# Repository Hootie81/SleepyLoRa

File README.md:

# SleepyLora Blinds System

A low-power wireless smart blinds system using LoRa to enable low power yet fast response to commands - 100% local control.

In July 2023 I set out the key requirements for the project
- 100% local control - no 3rd party servers etc.
- solar powered with up to 3days bad weather.
- back driveable without breaking.
- secure
- be cheap

This system is 100% local, no external access required at all.

A 2.5w 380mm x 70mm thin film flexible panel is enough to keep a 2000mah battery fully charged with less than 2 hours a day of sun. the 2000mah battery lasts about 10 days with no panel connected.

Key design requirement was for the blinds to still operate by hand, so a mechanism was developed that disengages the motor from the actuator once the move command is complete. [See disengage mechanism video](https://youtu.be/guv8YasCPMQ?si=FenjIrAAZN0NFrJr)

Position is sensed using a linear potentiometer thats connected to the actualing arm, so the blinds always know their position.

The actuators now use a PID controller to target a specified time for each move, this allows the motor to run significantly quieter and allows syncronsation of blinds with different operating forces/friction. All PID, PWM and timing settings are customisable.

All data packets are AES128 encrypted and hardened against replay attacks using 1 second interval TOTP, so no-one can open your blinds but you.
Costs are kept low by using cheap modules form china, assembled onto custom PCB's and housed in 3d printed parts.
The wired slaves are powered by the master, thus only a single battery and solar panel per system and a significant reduction in actuator cost too. 

This project includes electronics designs, firmware, and 3D printable parts for a complete DIY solution.

- [3D Parts Assembly Video](https://youtu.be/qfTnw-1N8DM?si=_8NIrLeuZx0titTB)
- [Electronics Assembly Video](https://youtu.be/dtDF-GL67Ew?si=iw6Ndi3xGu8mUtQ1)

This has been a couple of years in the making, and still very much a work in progress. If you find this project useful, please consider supporting my work:

Your support helps me keep building and maintaining open-source projects like this. Thank you!

---

### System

- **Gateway**:  
  Heltec Wireless Stick Lite V3, Connects to WiFi and MQTT, relays commands between Home Assistant and LoRa network. 
  Exposes a web portal for configuration and security key generation

- **Master**:  
  Blind actuator with a Heltec Wireless Stick Lite V3, voltage booster, motor driver, position sensor and RS485 module.
  Powered from a single cell lipo battery or USB.
  Can supply power to and control multiple slave devices via RS485.
  Exposes a web portal for configuration and firmware updates. (via button press or mqtt command)

- **Slave**:  
  Blind actuator with an ESP32-c3 module, motor driver, position sensor and RS485 module. 
  Powered by the Master
  Exposes a web portal for address configuration and OTA updates. (via button press or mqtt command)
  Connects to the master using a flat 6core telephone cable terminated with 4pin JST XH2.54 connectors
  
---

## Features

- **Long-range LoRa wireless communication**
- **Easy WiFi and MQTT Setup**
- **Easy key generation and sharing**
- **Home Assistant auto-discovery**
- **OTA firmware updates**
- **Configurable RS485 slave addressing**
- **Easy Open/Closed position setting via web portal**
- **PWM speed control with PID controller for quiet operation**
- **Auto calibration feature for disengage mechanism**
- **Low-power operation** 
- **3D-printable hardware** 
- **Easy to assemble electronics**
- **Open-source** 

---

## Project Structure

- **3d_prints/**  
  STL files for all mechanical parts 

- **Electronics/**  
  KiCad schematics, PCB layouts, and Gerber files for the master and slave boards.

- **SleepyLoraGateway/**  
  Firmware for the LoRa gateway device. Handles MQTT, Home Assistant integration, and LoRa communication. 

- **SleepyLoraMaster/**  
  Firmware for the master device, an actuator for one set of shutters, with the capability to power and control several slave devices via RS485.

- **SleepyLoraSlave/**  
  Firmware for the slave device, an actuator for one set of shutters and reports position/status.

---

## Getting Started

- Order all the parts/modules from Aliexpress, list in `Electronics/`
- Order PCB/s using the KiCad files in `Electronics/`
- Print and assemble the required parts from `3d_prints/`
- Solder the modules onto the PCB's
- Install electronics in 3d printed base
- Flash the appropriate firmware to each device:
  - Gateway: `SleepyLoraGateway/`
  - Master: `SleepyLoraMaster/`
  - Slave: `SleepyLoraSlave/`
- Configure the Gateway
  - Connect to the SleepyLoraGateway AP (pw: blind1234)
  - Set the WiFi, MQTT and NTP server information.
  - Set LoRa Region
  - Generate keys and download them. 
  - Save and reboot.
  - Gateway Connects to WiFi, MQTT and Sync's its time.
  - Gateway Publishes gateway metric discovery info and publishes data.
- Configure the Master/s
  - Connect to the SleeplyLoRaMaster AP (pw: blind1234)
  - Load the keys file downloaded above
  - Set Open and Closed limits
  - Save and reboot
  - Master sync's time with gateway
  - Master transmits Device metrics and status to Gateway.
  - Gateway publishes Blind discovery info, subscribes to MQTT topics, and publishes data every 60sec.
  - Master will transmit device metrics and status every minute.
- Check your HA MQTT integration, the Gatway, device and blind will magically appear after a minute or so. 
- Optionally - configure the slave/save
  - Connect the slave to the master 
  - Press the reset button on the master
  - Master will scan for slaves on initial bootup
  - Master transmits slave status to Gateway.
  - Gateway publishes Blind discovery info, subscribes to MQTT topics, and publishes data every 60sec.
  - Open web portal via MQTT or from the master web portal
  - Set Open and Closed limits
  - Master will poll slave and transmit status every minute.
  - Optionally - if a second slave is required
    - press the "Open Web Portal" button on the slave device in HomeAssistant
	- Connect to the SleeplyLoRaSlave AP (pw: blind1234)
	- Change the slave number
	- Save to flash
    - Scan for slaves via the master's web portal (Or press the reset button on the master)
    - Master will rescan for slaves

---

## Documentation

- Each firmware folder contains its own README with build and usage instructions.
- For wiring, assembly, and setup, see my videos on youtube or open an issue for help.

---

## ToDo

- Update slave firmware to use new motor controller library and updated web portal.
- Add feature to get/set all blind settings via MQTT.
- Design an enclosure to the battery and charger modules.
- Make an injection moulding option for the plastic parts.

---

## License

This project is open-source under the MIT License.  
See [LICENSE](LICENSE) for details.

---

## Credits

- Hardware, firmware, and 3D design by Chris Huitema
- Built with [PlatformIO](https://platformio.org/), [KiCad](https://kicad.org/), and [ESPAsyncWebServer](https://github.com/me-no-dev/ESPAsyncWebServer)

---

**Happy hacking and smart shading!**

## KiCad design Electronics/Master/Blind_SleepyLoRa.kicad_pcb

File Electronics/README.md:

# Electronics Folder — SleepyLoRa Project

This folder contains all the electronics design files, schematics, PCB layouts, and bills of materials (BOM) for the SleepyLoRa Blinds System. The electronics are designed to be easy to assemble, cost-effective, and reliable for DIY smart blinds control.

## Structure
- **bom.csv** — Common components and extras used across all devices (master, slave, gateway, etc.).
- **Master/** — Schematics, PCB layout, and device-specific BOM for the SleepyLoRaMaster (blind actuator/master controller).
- **Slave/** — Schematics, PCB layout, and device-specific BOM for the SleepyLoRaSlave (slave blind actuator).

Each device folder contains:
- KiCad project files (`.pro`, `.sch`, `.kicad_pcb`, etc.)
- Gerber files for PCB manufacturing
- Device-specific BOM (bill of materials)

## How to Use
1. Review `bom.csv` for the list of common components and extras needed for all devices.
2. For each device (Master, Slave, Gateway):
   - Open the corresponding folder for full schematics, PCB layout, and device-specific BOM.
   - Use the KiCad files to view or modify the design.
   - Use the Gerber files to order PCBs from your preferred manufacturer.
   - Use the device-specific BOM to order parts for that device.
3. Assemble the PCBs according to the schematics and BOMs.

## Notes
- All designs are open-source and provided as-is for DIY use.
- If you make improvements or modifications, please consider contributing back to the project!

## License
SPDX-License-Identifier: MIT

---
For questions or support, open an issue on the main [SleepyLoRa GitHub repository](https://github.com/Hootie81/SleepyLoRa).

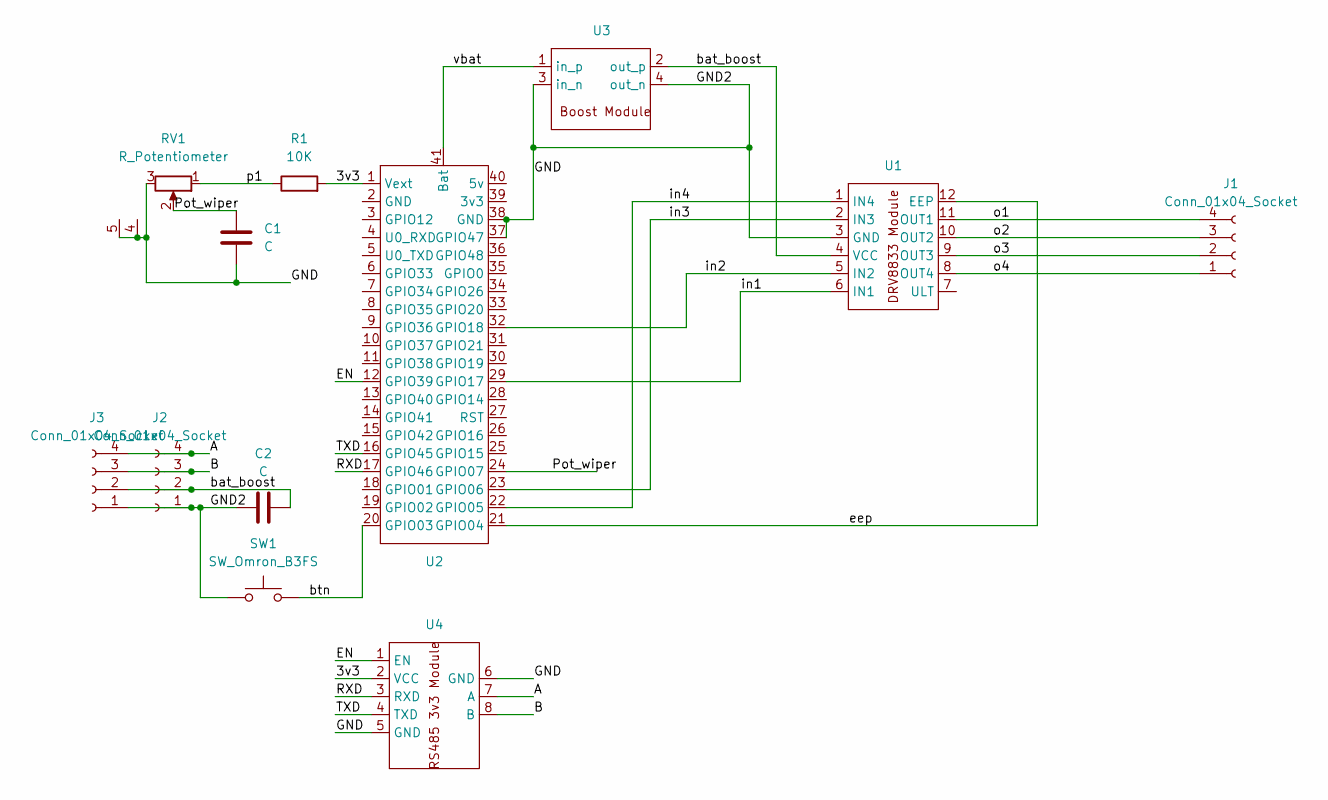
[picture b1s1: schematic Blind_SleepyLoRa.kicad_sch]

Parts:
C1, C2: C; C_Disc_D5.0mm_W2.5mm_P5.00mm
J1: Conn_01x04_Socket; JST_XH_B4B-XH-AM_1x04_P2.50mm_Vertical
J2, J3: Conn_01x04_Socket; JST_XH_B4B-XH-A_1x04_P2.50mm_Vertical
R1: 10K; R_Axial_DIN0309_L9.0mm_D3.2mm_P12.70mm_Horizontal
RV1: R_Potentiometer; linear_pot_128mm
SW1: SW_Omron_B3FS; SW_PUSH_6mm_H4.3mm
U1: drv8833_module
U2: WSL
U3: Boost_module
U4: RS485_3v3_module

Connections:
/3v3: R1.2, U2.1 (Vext), U4.2 (VCC)
/A: J2.4, J3.4, U4.7 (A)
/B: J2.3, J3.3, U4.8 (B)
/EN: U2.12 (GPIO39), U4.1 (EN)
/GND: C1.2, C2.2, J2.1, J3.1, RV1.3, RV1.4 (shld), RV1.5 (shld), SW1.1, U1.3 (GND), U2.37 (GPIO47), U2.38 (GND), U3.3 (in_n), U3.4 (out_n), U4.5 (GND), U4.6 (GND)
/Pot_wiper: C1.1, RV1.2, U2.24 (GPIO07)
/RXD: U2.17 (GPIO46), U4.3 (RXD)
/TXD: U2.16 (GPIO45), U4.4 (TXD)
/bat_boost: C2.1, J2.2, J3.2, U1.4 (VCC), U3.2 (out_p)
/btn: SW1.2, U2.20 (GPIO03)
/eep: U1.12 (EEP), U2.21 (GPIO04)
/in1: U1.6 (IN1), U2.29 (GPIO17)
/in2: U1.5 (IN2), U2.32 (GPIO18)
/in3: U1.2 (IN3), U2.23 (GPIO06)
/in4: U1.1 (IN4), U2.22 (GPIO05)
/o1: J1.4, U1.11 (OUT1)
/o2: J1.3, U1.10 (OUT2)
/o3: J1.2, U1.9 (OUT3)
/o4: J1.1, U1.8 (OUT4)
/p1: R1.1, RV1.1, U2.25 (GPIO15)
/vbat: U2.41 (Bat), U3.1 (in_p)

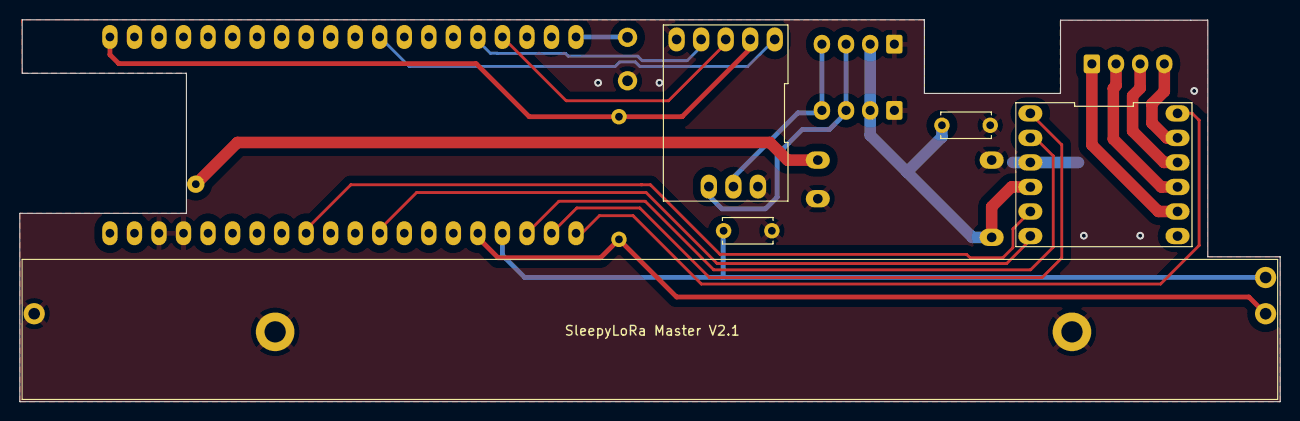
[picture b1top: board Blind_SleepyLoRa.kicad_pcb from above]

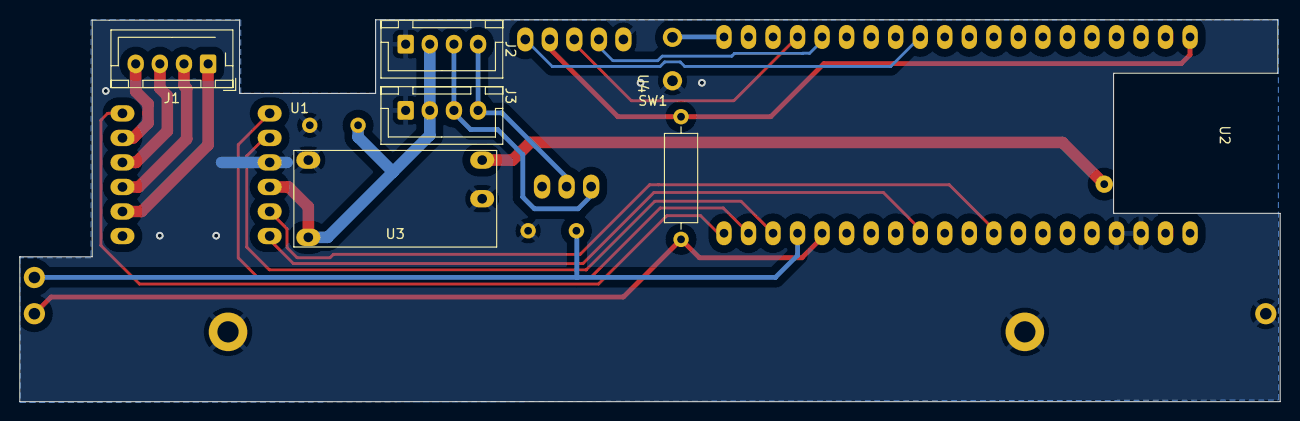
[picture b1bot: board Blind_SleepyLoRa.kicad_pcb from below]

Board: 2 copper layers, 130.5 x 39.5 mm, 12 parts (7 on the bottom side), 21 nets.

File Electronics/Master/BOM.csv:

ID,Part No,qty,link,notes
U1 ,DRV8833 module,1,https://www.aliexpress.com/item/1005007347094702.html,6pins each side not 7
U2,Heltec Wireless stick lite v3,1,https://www.aliexpress.com/item/1005005164155546.html,Ensure correct frequency for your area
,915MHz FPC Antenna PCB Anteana,1,https://www.aliexpress.com/item/1005006958686850.html,5mm x 75mm version
U3,Mini DC Boost Converter Board 3.7V to 12V Step Up Board Voltage Regulator PCB Board Electronic Voltage Module,1,https://www.aliexpress.com/item/1005006115043704.html,set to 5v output
U4,MAX3485 unidirection module 3.3v version,1,https://www.aliexpress.com/item/1005006186051306.html,"5pins 1 side, 3 on other"
R1,10k 1/4w resistor,1,,
SW1,Middle 2Pin 6x6x6mm Switch Tactile Push Button ,1,https://www.aliexpress.com/item/1005005917191424.html,
RV1,128mm B10K Single Channel Sliding Potentiometer Stroke 100mm Handle 8mm,1,https://www.aliexpress.com/item/1005005470862119.html,
"J1, J2, J3",JST XH2.54 4 Pin Terminals Plastic Shell Male Plug ,3,https://www.aliexpress.com/item/1005003422202370.html,
"C1, C2",100nf Ceramic cap 50v 0.1uf ,2,https://www.aliexpress.com/item/32971478818.html,

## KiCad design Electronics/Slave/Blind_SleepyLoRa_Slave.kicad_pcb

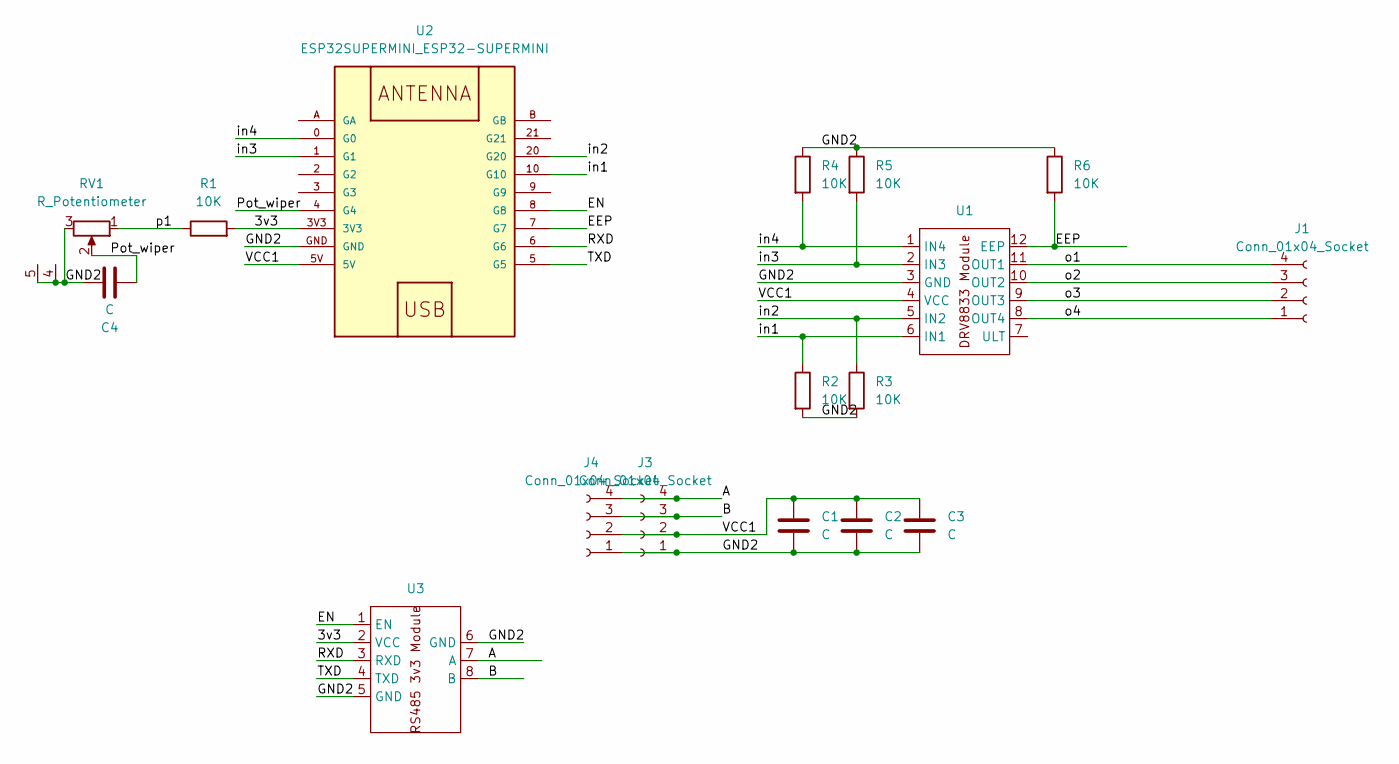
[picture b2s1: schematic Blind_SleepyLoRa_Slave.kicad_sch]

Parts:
C1, C2, C3, C4: C; C_Disc_D5.0mm_W2.5mm_P5.00mm
J1: Conn_01x04_Socket; JST_XH_B4B-XH-AM_1x04_P2.50mm_Vertical
J3, J4: Conn_01x04_Socket; JST_XH_B4B-XH-A_1x04_P2.50mm_Vertical
R1, R2, R3, R4, R5, R6: 10K; R_Axial_DIN0309_L9.0mm_D3.2mm_P12.70mm_Horizontal
RV1: R_Potentiometer; linear_pot_128mm
U1: drv8833_module
U2: ESP32SUPERMINI_ESP32-SUPERMINI
U3: RS485_3v3_module

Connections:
/3v3: R1.2, U2.3V3, U3.2 (VCC)
/A: J3.4, J4.4, U3.7 (A)
/B: J3.3, J4.3, U3.8 (B)
/EEP: R6.2, U1.12 (EEP), U2.7 (G7)
/EN: U2.8 (G8), U3.1 (EN)
/GND2: C1.2, C2.2, C3.2, C4.2, J3.1, J4.1, R2.2, R3.2, R4.1, R5.1, R6.1, RV1.3, RV1.4 (shld), RV1.5 (shld), U1.3 (GND), U2.GND, U3.5 (GND), U3.6 (GND)
/Pot_wiper: C4.1, RV1.2, U2.4 (G4)
/RXD: U2.6 (G6), U3.3 (RXD)
/TXD: U2.5 (G5), U3.4 (TXD)
/VCC1: C1.1, C2.1, C3.1, J3.2, J4.2, U1.4 (VCC), U2.5V
/in1: R2.1, U1.6 (IN1), U2.10 (G10)
/in2: R3.1, U1.5 (IN2), U2.20 (G20)
/in3: R5.2, U1.2 (IN3), U2.1 (G1)
/in4: R4.2, U1.1 (IN4), U2.0 (G0)
/o1: J1.4, U1.11 (OUT1)
/o2: J1.3, U1.10 (OUT2)
/o3: J1.2, U1.9 (OUT3)
/o4: J1.1, U1.8 (OUT4)
/p1: R1.1, RV1.1

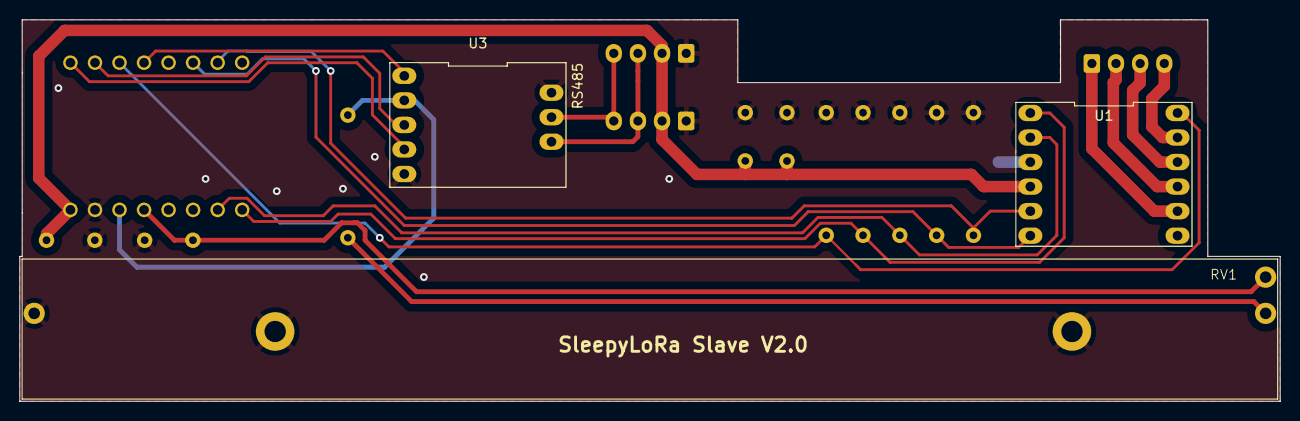
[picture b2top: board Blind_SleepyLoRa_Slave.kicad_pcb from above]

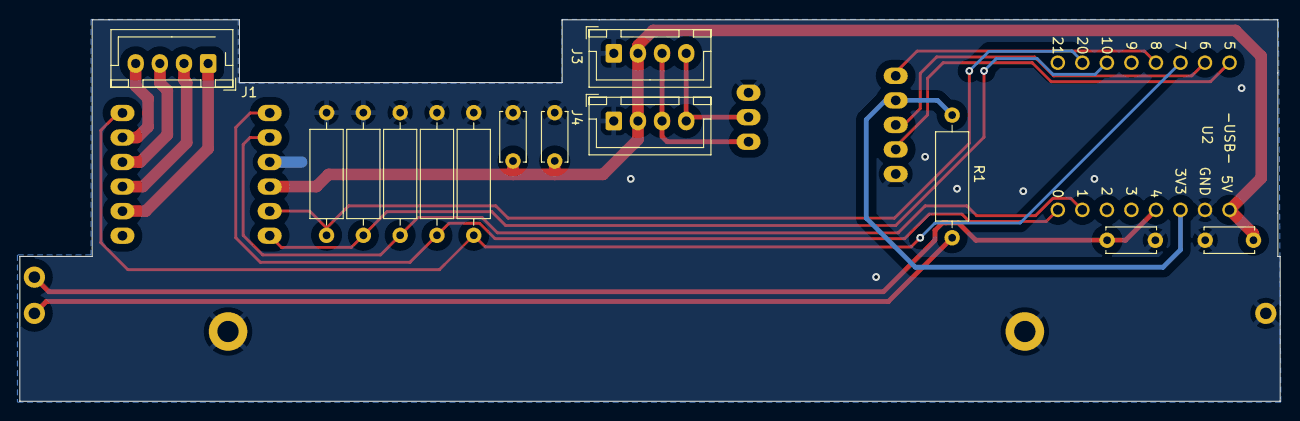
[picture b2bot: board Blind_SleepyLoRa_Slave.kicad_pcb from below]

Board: 2 copper layers, 130.5 x 39.5 mm, 17 parts (14 on the bottom side), 19 nets.

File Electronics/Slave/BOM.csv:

ID,Part No,qty,link,notes
U1 ,DRV8833 module,1,https://www.aliexpress.com/item/1005007347094702.html,6pins each side not 7
U2,ESP32 SuperMini Development Board ESP32-C3 Development Board,1,https://www.aliexpress.com/item/1005006350465839.html,
U3,MAX3485 unidirection module 3.3v version,1,https://www.aliexpress.com/item/1005006186051306.html,"5pins 1 side, 3 on other"
"R1,R2, R3, R4, R5, R6",10k 1/4w resistor,6,,"1required, 2-6 optional"
RV1,128mm B10K Single Channel Sliding Potentiometer Stroke 100mm Handle 8mm,1,https://www.aliexpress.com/item/1005005470862119.html,
"J1, J2, J3",JST XH2.54 4 Pin Terminals Plastic Shell Male Plug ,3,https://www.aliexpress.com/item/1005003422202370.html,
"C1, C2, C3, C4",100nf Ceramic cap 50v 0.1uf ,3,https://www.aliexpress.com/item/32971478818.html,

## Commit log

2025-06-01 Initial Upload of files
2025-06-01 Initial commit of Actuator device firmware
2025-06-01 Initial commit of the gateway firmware
2025-06-01 add licence and readme
2025-06-01 Add readme to electronics folder
2025-06-02 Added logging to gateway. make available via web portal
2025-06-04 Try and prevent log corruption. general code tidy up. improve OTP time stability by ensuring time used is as close to packet send time as possible
2025-06-05 Added missing screws for link bar cplamps to BOM
2025-06-05 Clean up OTP code. Minor changes to logic for position updates.
2025-06-05 Added reversed actuator cam for use when actuator is on the right hand side of the plantation shutter. Actuator will be extended when closed and retracted when open, which is reverse of the left hand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
2025-06-06 Add watchdog to Lora received messages
2025-06-06 improved logging messages. added mqtt watchdog. improved ntp logging
2025-06-06 corrected MQTT keepalive to 15sec
2025-06-07 adding pre-supported print files. chitubox file comepressed due to size limit
2025-06-07 Add print instructions
2025-06-10 Add links to assembly videos
2025-06-11 Correct pin assignment for V2 Master PCB.
2025-06-11 Improved logging and fix TX buffer filling while waiting for ack issue
2025-06-11 Add EN pin to slave device for new V2 PCB. Change from echo of received command to reply with status update
2025-06-11 Added buttons to webserver to set closed and open positions, values are saved to flash and loaded on boot.
2025-06-11 Add Open and Closed Calibration to MAster
2025-06-14 Add reference voltage to make position more accurate when motor running.
2025-06-15 Update master PCB to include ref voltage
2025-06-16 squash silly bug. ensure full rx buffer is processed before resending unack packet
2025-06-20 Add PWM speed control and improve nvs error handling.
2025-06-20 Add Config options to change stroke time and disengage time.
2025-06-21 Add calibration routine. improve position filter.
2025-06-23 significant changes, added dynamic PWM to set a target stroke time
2025-07-03 New BlindMotorController, web interface changes
2025-07-04 Update readme with new features and todo
2025-07-05 Add option to connect to WiFi or create an AP.
2025-07-12 Move common files to new lib folder. Update slave to use new libs
2025-08-07 Update Gateway offline status
2025-09-30 Config portal closing instantly fix.
